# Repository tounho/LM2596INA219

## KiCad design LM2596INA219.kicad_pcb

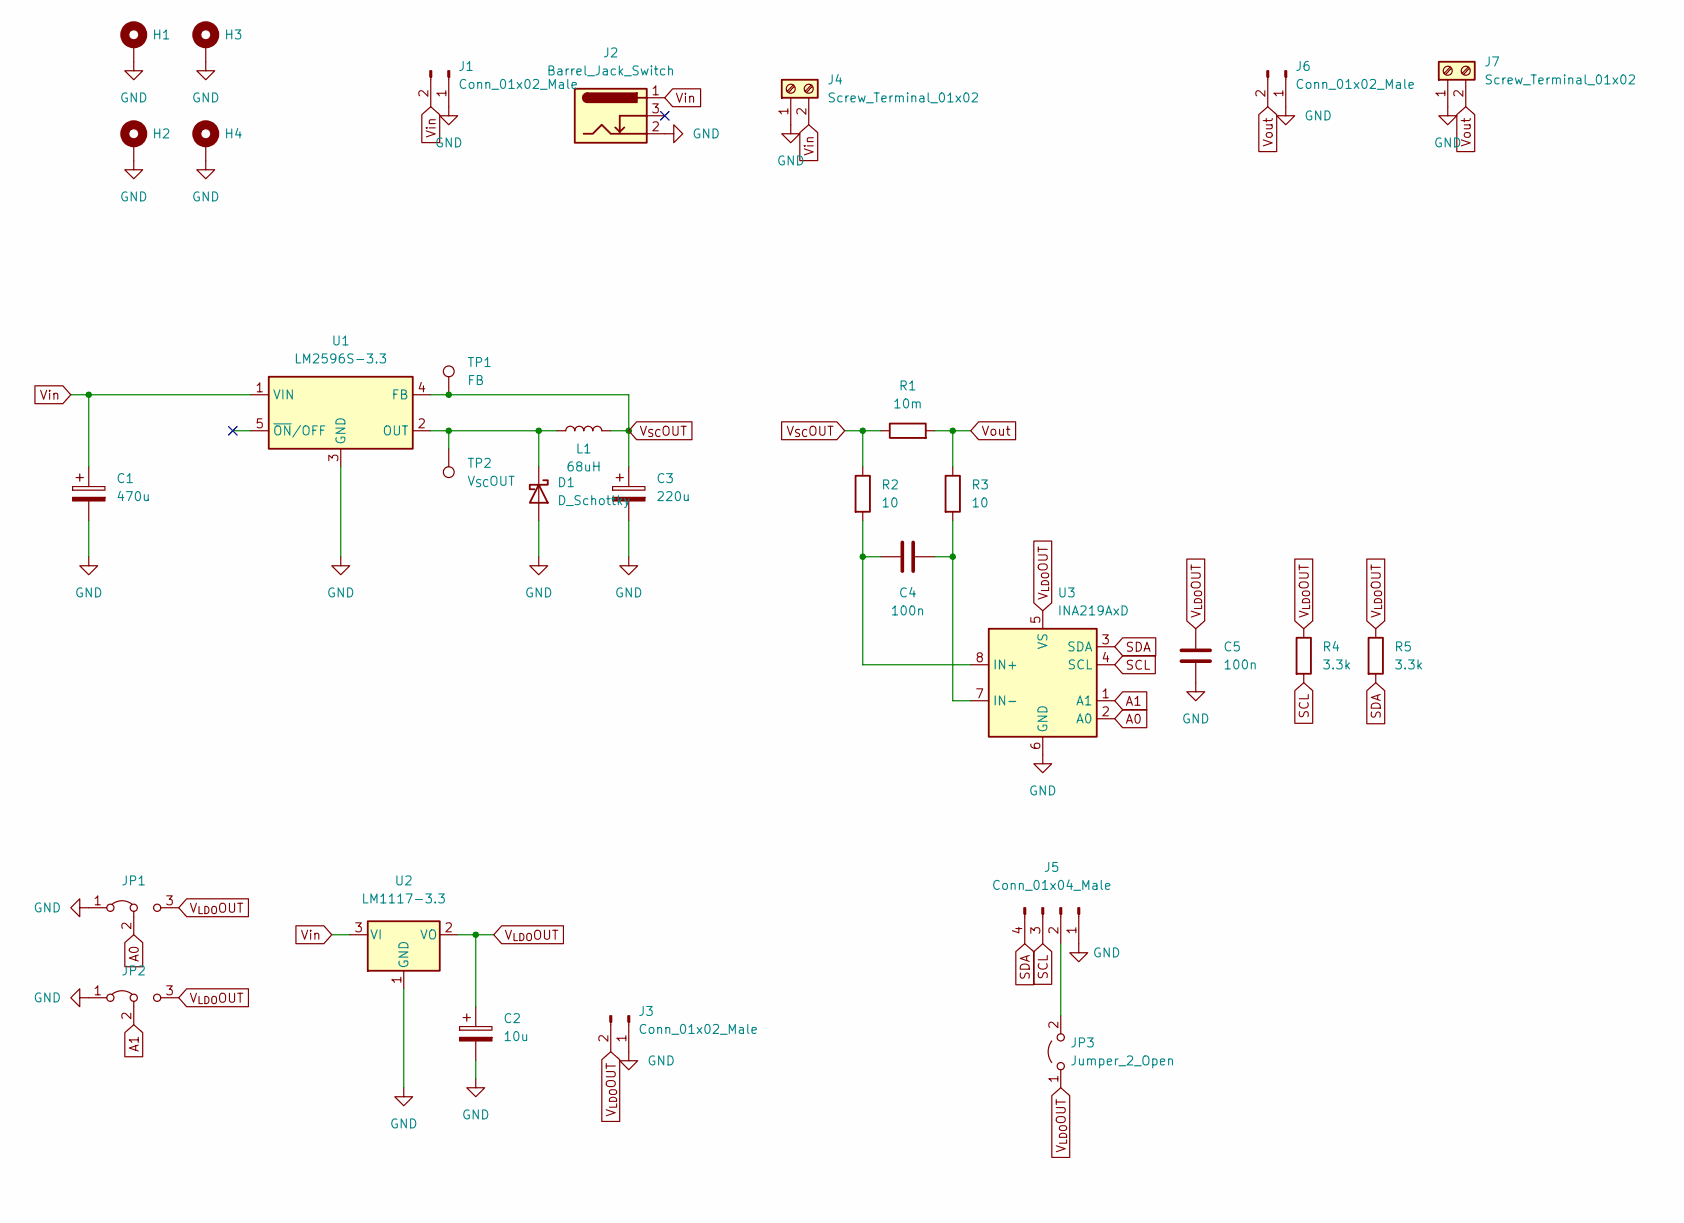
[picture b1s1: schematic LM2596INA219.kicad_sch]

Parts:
C1: 470u; CP_Radial_D8.0mm_P2.50mm
C2: 10u; CP_EIA-3528-12_Kemet-T_Pad1.50x2.35mm_HandSolder
C3: 220u; CP_Radial_D8.0mm_P2.50mm
C4, C5: 100n; C_0603_1608Metric_Pad1.08x0.95mm_HandSolder
D1: D_Schottky; D_SMA-SMB_Universal_Handsoldering
H1, H2, H3, H4: MountingHole_Pad; MountingHole_3.2mm_M3_DIN965_Pad
J1, J3, J6: Conn_01x02_Male; PinHeader_1x02_P2.54mm_Vertical
J2: Barrel_Jack_Switch; BarrelJack_Horizontal
J4, J7: Screw_Terminal_01x02; TerminalBlock_bornier-2_P5.08mm
J5: Conn_01x04_Male; PinHeader_1x04_P2.54mm_Vertical
JP1, JP2: Jumper_3_Bridged12; PinHeader_1x03_P2.54mm_Vertical
JP3: Jumper_2_Open; SolderJumper-2_P1.3mm_Open_RoundedPad1.0x1.5mm
L1: 68uH; L_12x12mm_H8mm
R1: 10m; R_1206_3216Metric_Pad1.30x1.75mm_HandSolder
R2, R3: 10; R_0603_1608Metric_Pad0.98x0.95mm_HandSolder
R4, R5: 3.3k; R_0603_1608Metric_Pad0.98x0.95mm_HandSolder
TP1: FB; TestPoint_Pad_D1.0mm
TP2: V_{SC}OUT; TestPoint_Pad_D1.0mm
U1: LM2596S-3.3; TO-263-5_TabPin3
U2: LM1117-3.3; SOT-223-3_TabPin2
U3: INA219AxD; SOIC-8_3.9x4.9mm_P1.27mm

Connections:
A0: JP1.2 (C), U3.2 (A0)
A1: JP2.2 (C), U3.1 (A1)
GND: C1.2, C2.2, C3.2, C5.1, D1.2 (A), H1.1, H2.1, H3.1, H4.1, J1.1, J2.2, J3.1, J4.1, J5.1, J6.1, J7.1, JP1.1 (A), JP2.1 (A), U1.3 (GND), U2.1 (GND), U3.6 (GND)
unnamed: C4.1, R2.2, U3.8 (IN+)
unnamed: C4.2, R3.2, U3.7 (IN-)
unnamed: D1.1 (K), L1.1, TP2.1, U1.2 (OUT)
unnamed: J5.2, JP3.2 (B)
SCL: J5.3, R4.2, U3.4 (SCL)
SDA: J5.4, R5.2, U3.3 (SDA)
V_{LDO}OUT: C2.1, C5.2, J3.2, JP1.3 (B), JP2.3 (B), JP3.1 (A), R4.1, R5.1, U2.2 (VO), U3.5 (VS)
V_{SC}OUT: C3.1, L1.2, R1.1, R2.1, TP1.1, U1.4 (FB)
Vin: C1.1, J1.2, J2.1, J4.2, U1.1 (VIN), U2.3 (VI)
Vout: J6.2, J7.2, R1.2, R3.1

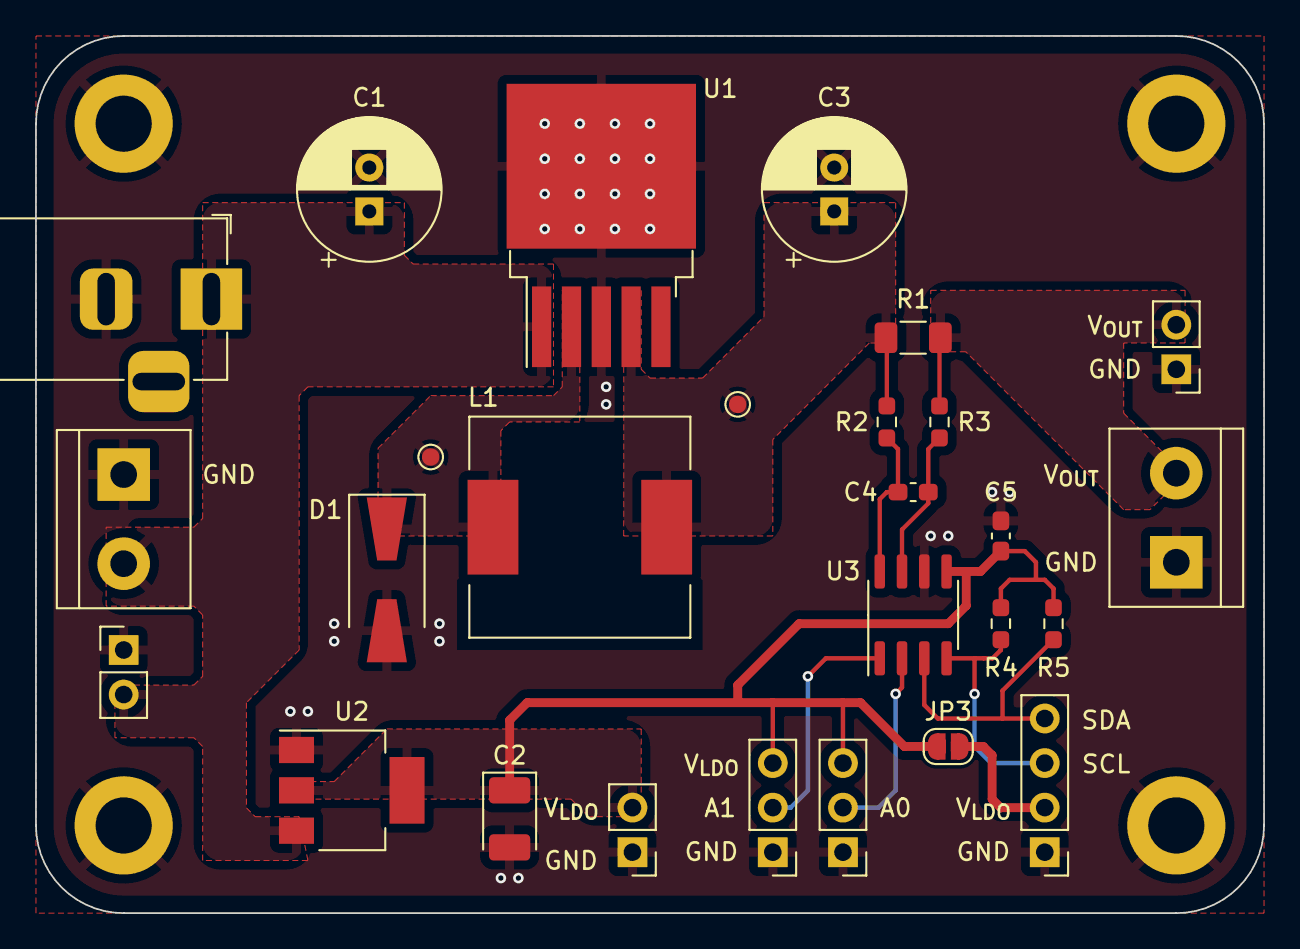
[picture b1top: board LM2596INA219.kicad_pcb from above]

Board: 2 copper layers, 70.0 x 50.0 mm, 31 parts (0 on the bottom side), 13 nets.
